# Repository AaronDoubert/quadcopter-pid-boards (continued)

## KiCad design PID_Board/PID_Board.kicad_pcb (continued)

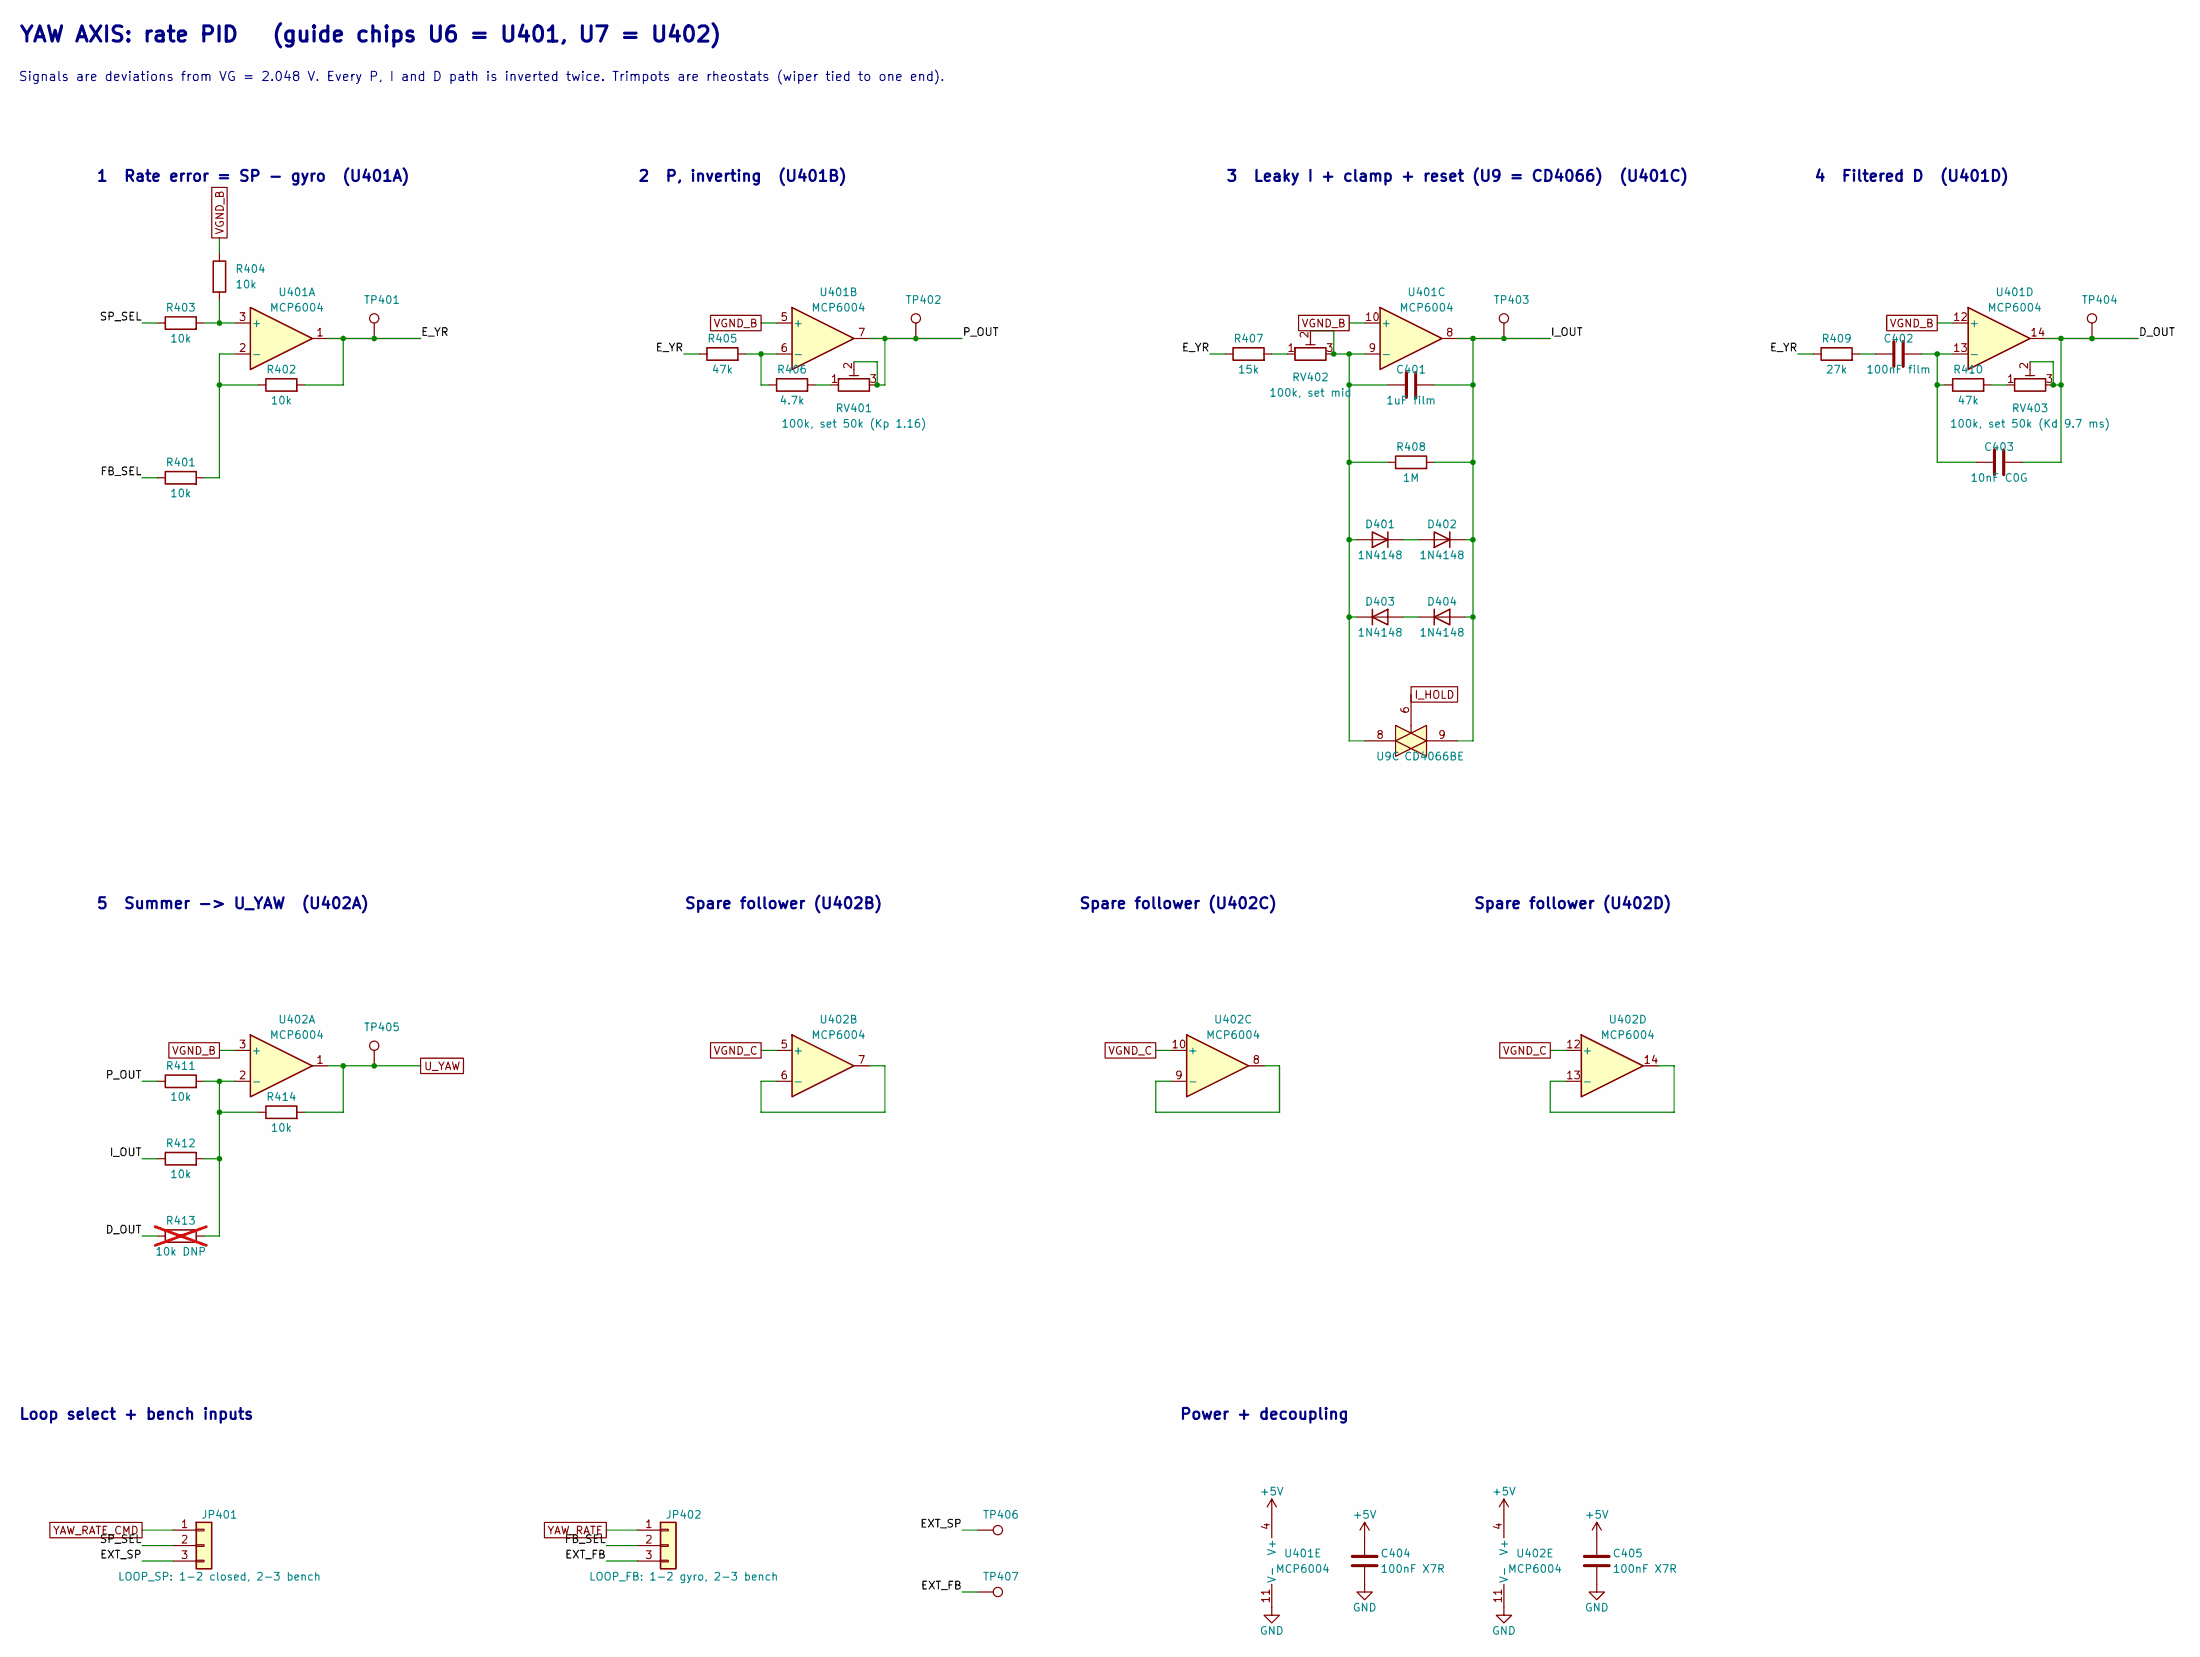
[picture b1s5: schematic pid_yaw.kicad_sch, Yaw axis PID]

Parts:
C401: 1uF film; C_Rect_L7.2mm_W5.5mm_P5.00mm_FKS2_FKP2_MKS2_MKP2
C402: 100nF film; C_Rect_L7.2mm_W2.5mm_P5.00mm_FKS2_FKP2_MKS2_MKP2
C403: 10nF C0G; C_Disc_D5.0mm_W2.5mm_P5.00mm
C404, C405: 100nF X7R; C_Disc_D5.0mm_W2.5mm_P5.00mm
D401, D402, D403, D404: 1N4148; D_DO-35_SOD27_P7.62mm_Horizontal
JP401: LOOP_SP: 1-2 closed, 2-3 bench; PinHeader_1x03_P2.54mm_Vertical
JP402: LOOP_FB: 1-2 gyro, 2-3 bench; PinHeader_1x03_P2.54mm_Vertical
R401, R402, R403, R404, R411, R412, R414: 10k; R_Axial_DIN0207_L6.3mm_D2.5mm_P7.62mm_Horizontal
R405, R410: 47k; R_Axial_DIN0207_L6.3mm_D2.5mm_P7.62mm_Horizontal
R406: 4.7k; R_Axial_DIN0207_L6.3mm_D2.5mm_P7.62mm_Horizontal
R407: 15k; R_Axial_DIN0207_L6.3mm_D2.5mm_P7.62mm_Horizontal
R408: 1M; R_Axial_DIN0207_L6.3mm_D2.5mm_P7.62mm_Horizontal
R409: 27k; R_Axial_DIN0207_L6.3mm_D2.5mm_P7.62mm_Horizontal
R413: 10k DNP; R_Axial_DIN0207_L6.3mm_D2.5mm_P7.62mm_Horizontal; not fitted
RV401: 100k, set 50k (Kp 1.16); Potentiometer_Bourns_3296W_Vertical
RV402: 100k, set mid; Potentiometer_Bourns_3296W_Vertical
RV403: 100k, set 50k (Kd 9.7 ms); Potentiometer_Bourns_3296W_Vertical
TP401: E_YR; PinHeader_1x01_P2.54mm_Vertical
TP402: P_OUT; PinHeader_1x01_P2.54mm_Vertical
TP403: I_OUT; PinHeader_1x01_P2.54mm_Vertical
TP404: D_OUT; PinHeader_1x01_P2.54mm_Vertical
TP405: U_YAW; PinHeader_1x01_P2.54mm_Vertical
TP406: EXT_SP; PinHeader_1x01_P2.54mm_Vertical
TP407: EXT_FB; PinHeader_1x01_P2.54mm_Vertical
U9: CD4066BE; DIP-14_W7.62mm
U401, U402: MCP6004; DIP-14_W7.62mm

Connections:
+5V: C404.1, C405.1, U401.4 (V+), U402.4 (V+); also elsewhere on the board
/PID_Yaw/D_OUT: C403.2, R413.1, RV403.2, RV403.3, TP404.1, U401.14
/PID_Yaw/EXT_FB: JP402.3, TP407.1
/PID_Yaw/EXT_SP: JP401.3, TP406.1
/PID_Yaw/E_YR: R402.2, R405.1, R407.1, R409.1, TP401.1, U401.1
/PID_Yaw/FB_SEL: JP402.2, R401.1
/PID_Yaw/I_OUT: C401.2, D402.1 (K), D404.2 (A), R408.2, R412.1, TP403.1, U9.9, U401.8
/PID_Yaw/P_OUT: R411.1, RV401.2, RV401.3, TP402.1, U401.7
/PID_Yaw/SP_SEL: JP401.2, R403.1
GND: C404.2, C405.2, U401.11 (V-), U402.11 (V-); also elsewhere on the board
I_HOLD: U9.6; also elsewhere on the board
unnamed: C402.1, R409.2
unnamed: C401.1, D401.2 (A), D403.1 (K), R408.1, RV402.2, RV402.3, U9.8, U401.9 (-)
unnamed: D401.1 (K), D402.2 (A)
unnamed: D403.2 (A), D404.1 (K)
unnamed: R406.2, RV401.1
unnamed: R407.2, RV402.1
unnamed: R410.2, RV403.1
unnamed: R403.2, R404.2, U401.3 (+)
unnamed: R401.2, R402.1, U401.2 (-)
unnamed: R405.2, R406.1, U401.6 (-)
unnamed: C402.2, C403.1, R410.1, U401.13 (-)
unnamed: R411.2, R412.2, R413.2, R414.1, U402.2 (-)
unnamed: U402.6 (-), U402.7
unnamed: U402.8, U402.9 (-)
unnamed: U402.13 (-), U402.14
U_YAW: R414.2, TP405.1, U402.1; also elsewhere on the board
VGND_B: R404.1, U401.5 (+), U401.10 (+), U401.12 (+), U402.3 (+); also elsewhere on the board
VGND_C: U402.5 (+), U402.10 (+), U402.12 (+); also elsewhere on the board
YAW_RATE: JP402.1; also elsewhere on the board
YAW_RATE_CMD: JP401.1; also elsewhere on the board

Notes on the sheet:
YAW AXIS: rate PID (guide chips U6 = U401, U7 = U402)
Signals are deviations from VG = 2.048 V. Every P, I and D path is inverted twice. Trimpots are rheostats (wiper tied to one end).
1 Rate error = SP - gyro (U401A)
2 P, inverting (U401B)
3 Leaky I + clamp + reset (U9 = CD4066) (U401C)
4 Filtered D (U401D)
5 Summer -> U_YAW (U402A)
Spare follower (U402B)
Spare follower (U402C)
Spare follower (U402D)
Loop select + bench inputs
Power + decoupling

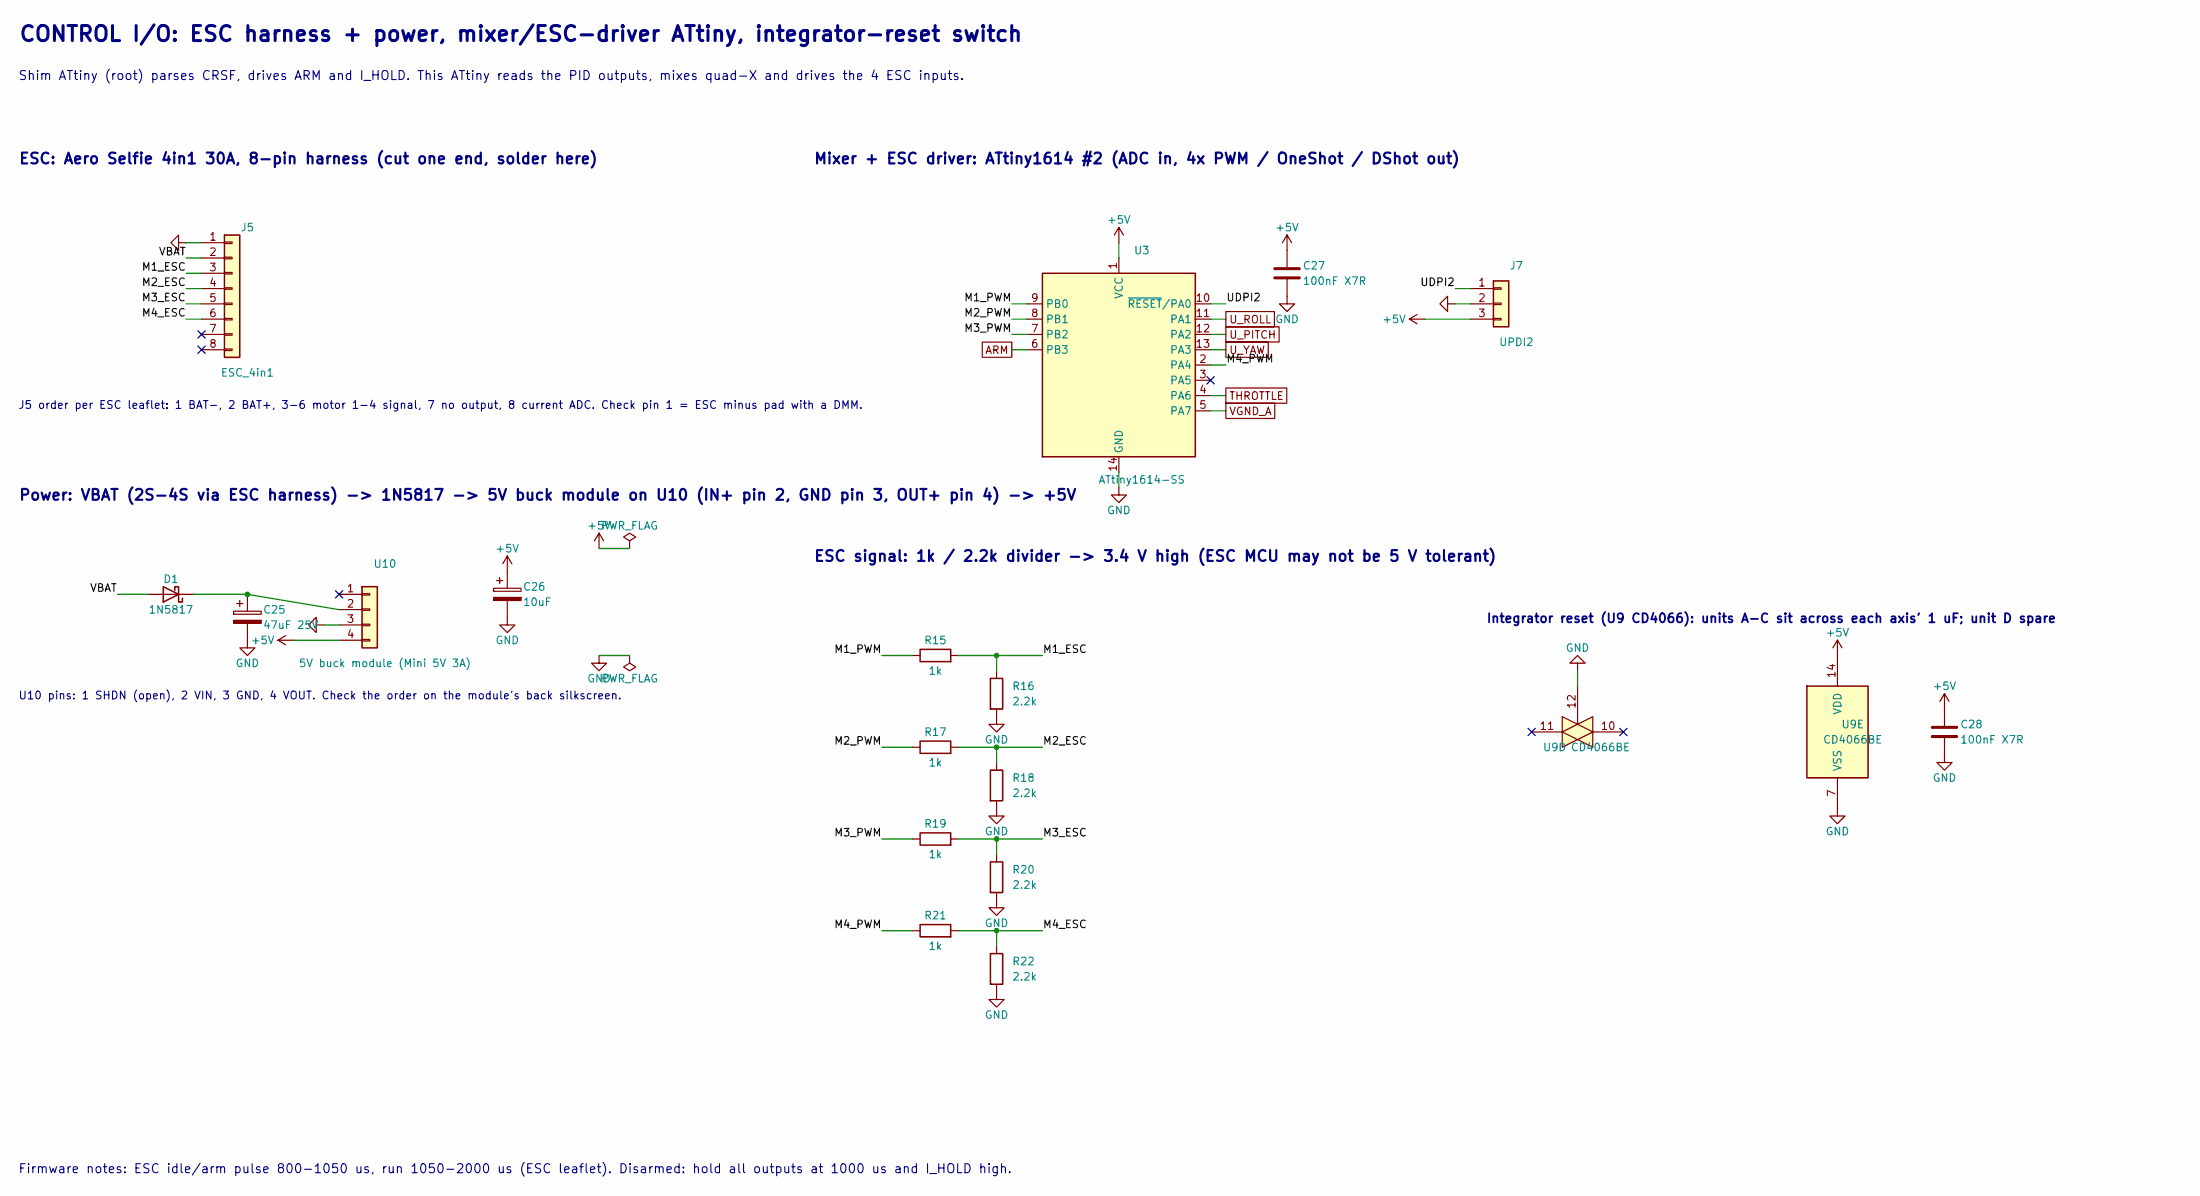
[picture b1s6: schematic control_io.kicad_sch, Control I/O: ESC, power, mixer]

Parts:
C25: 47uF 25V; CP_Radial_D5.0mm_P2.00mm
C26: 10uF; CP_Radial_D5.0mm_P2.00mm
C27, C28: 100nF X7R; C_Disc_D5.0mm_W2.5mm_P5.00mm
D1: 1N5817; D_DO-41_SOD81_P10.16mm_Horizontal
J5: ESC_4in1; PinHeader_1x08_P2.54mm_Vertical
J7: UPDI2; PinHeader_1x03_P2.54mm_Vertical
R15, R17, R19, R21: 1k; R_Axial_DIN0207_L6.3mm_D2.5mm_P7.62mm_Horizontal
R16, R18, R20, R22: 2.2k; R_Axial_DIN0207_L6.3mm_D2.5mm_P7.62mm_Horizontal
U3: ATtiny1614-SS; SOIC-14_3.9x8.7mm_P1.27mm
U9: CD4066BE; DIP-14_W7.62mm
U10: 5V buck module (Mini 5V 3A); PinHeader_1x04_P2.54mm_Vertical

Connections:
+5V: C26.1, C27.1, C28.1, J7.3, U3.1 (VCC), U9.14 (VDD), U10.4; also elsewhere on the board
/Control_IO/M1_ESC: J5.3, R15.2, R16.1
/Control_IO/M1_PWM: R15.1, U3.9 (PB0)
/Control_IO/M2_ESC: J5.4, R17.2, R18.1
/Control_IO/M2_PWM: R17.1, U3.8 (PB1)
/Control_IO/M3_ESC: J5.5, R19.2, R20.1
/Control_IO/M3_PWM: R19.1, U3.7 (PB2)
/Control_IO/M4_ESC: J5.6, R21.2, R22.1
/Control_IO/M4_PWM: R21.1, U3.2 (PA4)
/Control_IO/UDPI2: J7.1, U3.10 (~RESET/PA0)
/Control_IO/VBAT: D1.2 (A), J5.2
ARM: U3.6 (PB3); also elsewhere on the board
GND: C25.2, C26.2, C27.2, C28.2, J5.1, J7.2, R16.2, R18.2, R20.2, R22.2, U3.14 (GND), U9.7 (VSS), U9.12, U10.3; also elsewhere on the board
unnamed: C25.1, D1.1 (K), U10.2
THROTTLE: U3.4 (PA6); also elsewhere on the board
U_PITCH: U3.12 (PA2); also elsewhere on the board
U_ROLL: U3.11 (PA1); also elsewhere on the board
U_YAW: U3.13 (PA3); also elsewhere on the board
VGND_A: U3.5 (PA7); also elsewhere on the board

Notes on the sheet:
CONTROL I/O: ESC harness + power, mixer/ESC-driver ATtiny, integrator-reset switch
Shim ATtiny (root) parses CRSF, drives ARM and I_HOLD. This ATtiny reads the PID outputs, mixes quad-X and drives the 4 ESC inputs.
ESC: Aero Selfie 4in1 30A, 8-pin harness (cut one end, solder here)
J5 order per ESC leaflet: 1 BAT-, 2 BAT+, 3-6 motor 1-4 signal, 7 no output, 8 current ADC. Check pin 1 = ESC minus pad with a DMM.
Power: VBAT (2S-4S via ESC harness) -> 1N5817 -> 5V buck module on U10 (IN+ pin 2, GND pin 3, OUT+ pin 4) -> +5V
U10 pins: 1 SHDN (open), 2 VIN, 3 GND, 4 VOUT. Check the order on the module's back silkscreen.
Mixer + ESC driver: ATtiny1614 #2 (ADC in, 4x PWM / OneShot / DShot out)
ESC signal: 1k / 2.2k divider -> 3.4 V high (ESC MCU may not be 5 V tolerant)
Integrator reset (U9 CD4066): units A-C sit across each axis' 1 uF; unit D spare
Firmware notes: ESC idle/arm pulse 800-1050 us, run 1050-2000 us (ESC leaflet). Disarmed: hold all outputs at 1000 us and I_HOLD high.

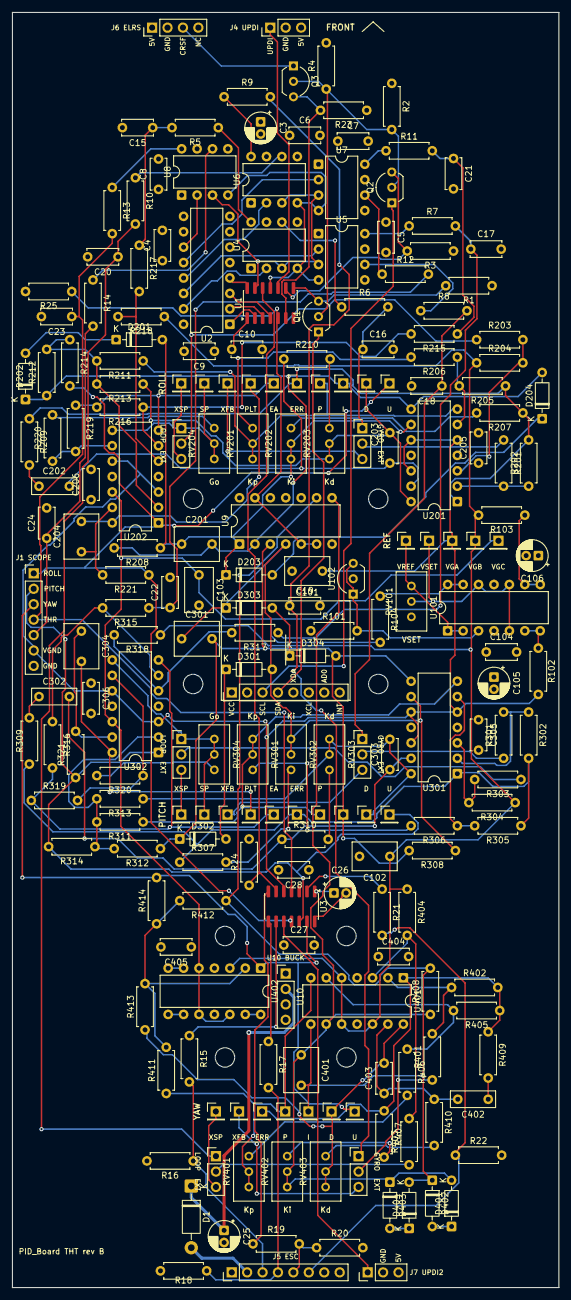
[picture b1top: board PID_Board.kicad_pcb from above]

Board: 4 copper layers, 90.0 x 210.0 mm, 228 parts (0 on the bottom side), 144 nets.

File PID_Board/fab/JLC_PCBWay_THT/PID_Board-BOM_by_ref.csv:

"Refs","Value","Footprint","Qty","DNP"
"C3-C10,C15-C28,C101-C106,C201-C206,C301-C306,C401-C405","100nF X7R,100nF film,10nF C0G,10uF,1uF,1uF film,470nF film,47uF 25V","Capacitor_THT:CP_Radial_D5.0mm_P2.00mm,Capacitor_THT:C_Disc_D5.0mm_W2.5mm_P5.00mm,Capacitor_THT:C_Rect_L7.2mm_W2.5mm_P5.00mm_FKS2_FKP2_MKS2_MKP2,Capacitor_THT:C_Rect_L7.2mm_W4.5mm_P5.00mm_FKS2_FKP2_MKS2_MKP2,Capacitor_THT:C_Rect_L7.2mm_W5.5mm_P5.00mm_FKS2_FKP2_MKS2_MKP2","45",""
"D1,D201-D204,D301-D304,D401-D404","1N4148,1N5817","Diode_THT:D_DO-35_SOD27_P7.62mm_Horizontal,Diode_THT:D_DO-41_SOD81_P10.16mm_Horizontal","13",""
"H1-H8","MountingHole","MountingHole:MountingHole_3.2mm_M3","8",""
"J1,J2,J4-J7","Axis_Mon,ELRS_RX,ESC_4in1,IMU_GY521,UPDI,UPDI2","Connector_PinHeader_2.54mm:PinHeader_1x03_P2.54mm_Vertical,Connector_PinHeader_2.54mm:PinHeader_1x04_P2.54mm_Vertical,Connector_PinHeader_2.54mm:PinHeader_1x07_P2.54mm_Vertical,Connector_PinHeader_2.54mm:PinHeader_1x08_P2.54mm_Vertical","6",""
"JP201,JP202,JP301,JP302,JP401,JP402","LOOP_FB: 1-2 gyro, 2-3 bench,LOOP_SP: 1-2 closed, 2-3 bench","Connector_PinHeader_2.54mm:PinHeader_1x03_P2.54mm_Vertical","6",""
"Q1-Q3","2N7000","Package_TO_SOT_THT:TO-92_Inline_Wide","3",""
"R1-R25,R101-R104,R201-R221,R301-R321,R401-R414","100,10k,10k DNP,15k,1M,1k,2.2k,20k,22k,27k,33k,4.7k,47k","Resistor_THT:R_Axial_DIN0207_L6.3mm_D2.5mm_P10.16mm_Horizontal","85","DNP"
"RV101,RV201-RV204,RV301-RV304,RV401-RV403","100k, set 50k (Kd 9.7 ms),100k, set 50k (Kp 1.16),100k, set 67k (Ki 10/s),100k, set mid,10k (wiper-GND 8.1k),50k, set 25k (Go 1.75)","Potentiometer_THT:Potentiometer_Bourns_3296W_Vertical","12",""
"TP101-TP105,TP201-TP210,TP301-TP310,TP401-TP407","D_OUT,EXT_FB,EXT_SP,E_A,E_PR,E_RR,E_YR,I_OUT,PITCH_RATE_SP,PLANT_OUT,P_OUT,ROLL_RATE_SP,U_PITCH,U_ROLL,U_YAW,VGND_A,VGND_B,VGND_C,VREF_BUF,VSET","Connector_PinHeader_2.54mm:PinHeader_1x01_P2.54mm_Vertical","32",""
"U1-U10,U101,U102,U201,U202,U301,U302,U401,U402","74HC138,ATtiny1614-SS,CD4066BE,MCP4822,MCP6004,Pololu D24V5F5,TL431ACLPG","Connector_PinHeader_2.54mm:PinHeader_1x04_P2.54mm_Vertical,Package_DIP:DIP-14_W7.62mm,Package_DIP:DIP-16_W7.62mm,Package_DIP:DIP-8_W7.62mm,Package_SO:SOIC-14_3.9x8.7mm_P1.27mm,Package_TO_SOT_THT:TO-92_Inline_Wide","18",""

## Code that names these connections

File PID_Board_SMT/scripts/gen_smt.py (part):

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                 ref_xy=(x + 11.43, y - 11.43), val_xy=(x + 11.43, y + 11.43), just="left")
    sh.pwr("+5V", *t["17"][:2]); sh.pwr("GND", *t["7"][:2])
    sh.expect("+5V", f"{ref}.17"); sh.expect("GND", f"{ref}.7")
    sh.pin_net(t, ref, "5", "SCL_5V")
    sh.pin_net(t, ref, "6", "SDA_5V")
    sh.pin_net(t, ref, "15", "+5V", stub=5.08)
    sh.pin_net(t, ref, "4", a0, stub=5.08)
    sh.pin_net(t, ref, "16", a1, stub=10.16)
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    sh.wire((xR, O[1]), (tpx, O[1]), (X + 22.86, O[1]))
    sh.junc(tpx, O[1])
    sh.place("Connector", "TestPoint", "TP101", "VREF_BUF", FP["TP"], tpx, O[1], 0, ref_xy=(tpx + 1.27, O[1] - 6.35), hide_val=True)
    sh.label("VREF_BUF", X + 22.86, O[1], 0)
    sh.expect("VREF_BUF", "U101.1", "U101.2", "TP101.1")
    # VSET divider: VREF_BUF - 47.5k - VSET - (U103 ch3 rheostat + 165k) - GND.
    # Code 128 (power-on) ~ 2.044 V; range 1.94..2.12 V; 0.67 mV per step.
    py = 71.12
    sh.text("VSET divider (digital trim)", 121.92, 45.72, 1.8)
    sh.wire((124.46, py), (127.0, py))
    sh.label("VREF_BUF", 124.46, py, 180)
    sh.chain([("R", "R105", "47.5k", FP["R"])], 127.0, 139.7, py, "VREF_BUF", "VSET")
    sh.wire((139.7, py), (139.7, py - 5.08))
    sh.label("VSET", 139.7, py - 5.08, 90)
    sh.chain([("DPOT", "U103", 4, "VSET trim: ch3, code 128 = 2.044 V"), ("R", "R106", "165k", FP["R"])],
             139.7, 175.26, py, "VSET", "GND")
    sh.junc(139.7, py)
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    testpoint(sh, "TP102", "VSET", 160.02, 55.88)
    t = sh.place("Device", "C", "C107", "100nF X7R", FP["C0603"], 167.64, 91.44, 0,
                 ref_xy=(170.18, 90.17), val_xy=(170.18, 92.71), just="left")
    sh.pin_net(t, "C107", "1", "VSET")
    sh.pin_net(t, "C107", "2", "GND", stub=0)
    # U103 control unit (I2C 0x2E); its channels 0-2 sit on the yaw sheet
    sh.text("U103 MCP4451: I2C 0x2E (A1=1, A0=0). ch0-2 = yaw P/I/D, ch3 = VSET", 121.92, 101.6, 1.5)
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        P, M, O = t[pp][:2], t[pm][:2], t[po][:2]
        xL, xR = X - 10.16, X + 10.16
        sh.wire(P, (xL, P[1]))
        sh.label("VSET", xL, P[1], 180)
        sh.wire(M, (xL, M[1]), (xL, M[1] + 5.08), (xR, M[1] + 5.08), (xR, O[1]))
        sh.wire(O, (xR, O[1]))
        rref, cref, tpref = f"R1{2 + i:02d}", f"C1{1 + i:02d}", f"TP1{3 + i:02d}"
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                         ref_xy=(X + 2.54, r2 - 7.62), val_xy=(X + 2.54, r2 - 5.08))
            P, M, O = t[pp][:2], t[pm][:2], t[po][:2]
            xL, xR = X - 10.16, X + 10.16
            sh.wire(P, (xL, P[1])); sh.label("VGND_C", xL, P[1], 180)
            sh.wire(M, (xL, M[1]), (xL, M[1] + 5.08), (xR, M[1] + 5.08), (xR, O[1]), O)
            sh.expect("VGND_C", f"{ub}.{pp}")
            sh.expect(f"~{ub}.{po}", f"{ub}.{po}", f"{ub}.{pm}")
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    sh.text("UPDI (Adafruit UPDI Friend)", 22.86, 40.64, 1.8)
    t = sh.place("Connector_Generic", "Conn_01x03", "J4", "UPDI", FP["H3"], 50.8, 55.88, 0,
                 ref_xy=(53.34, 49.53), val_xy=(53.34, 62.23))
    sh.pin_net(t, "J4", "1", "UDPI")
    sh.pin_net(t, "J4", "2", "GND", stub=2.54)
    sh.pin_net(t, "J4", "3", "+5V", stub=7.62)
    decouple(sh, 71.12, 55.88, "C3", "10uF 25V", FP["C0805"])
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                 ref_xy=(48.26, 92.71), val_xy=(48.26, 107.95))
    sh.pin_net(t, "J6", "1", "+5V", stub=7.62)
    sh.pin_net(t, "J6", "2", "GND", stub=2.54)
    sh.pin_net(t, "J6", "3", "CRSF_3V3")
    sh.pin_net(t, "J6", "4", None, stub=0)
    sh.text("J6: 1 5V, 2 GND, 3 receiver TX, 4 receiver RX (unused)", 22.86, 113.03, 1.3, False)
    qx, qy = 66.04, 88.9
    t = sh.place("Transistor_FET", "Q_NMOS_GSD", "Q3", "BSS138", FP["SOT23"], qx, qy, 270,
                 ref_xy=(qx + 3.81, qy + 6.35), val_xy=(qx + 3.81, qy + 8.89))
    G, S, Dn = t["1"][:2], t["2"][:2], t["3"][:2]   # SOT-23: 1 G, 2 S, 3 D
    sh.wire(S, (S[0] - 5.08, S[1])); sh.label("CRSF_3V3", S[0] - 5.08, S[1], 180)
    sh.wire(G, (G[0], G[1] - 2.54)); sh.label("GATE_BIAS", G[0], G[1] - 2.54, 90)
    node = (Dn[0] + 7.62, Dn[1])
    sh.wire(Dn, node, (node[0] + 5.08, node[1])); sh.junc(*node)
    sh.label("CRSF_5V", node[0] + 5.08, node[1], 0)
    top, bot, _ = sh.two("R", "R23", "2.2k", FP["R"], node[0], node[1] - 7.62, horizontal=False)
    sh.wire(bot, node); sh.pwr("+5V", *top)
    sh.expect("CRSF_3V3", "Q3.2"); sh.expect("GATE_BIAS", "Q3.1"); sh.expect("CRSF_5V", "Q3.3", "R23.2")
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                 ref_xy=(302.26, 55.88), val_xy=(302.26, 80.01))
    sh.pin_net(t, "J2", "1", "+5V", stub=7.62)
    sh.pin_net(t, "J2", "2", "GND", stub=2.54)
    sh.pin_net(t, "J2", "3", "SCL_3V3")
    sh.pin_net(t, "J2", "4", "SDA_3V3")
    for num in ("5", "6", "7", "8"):
        sh.pin_net(t, "J2", num, None, stub=0)
    sh.text("J2 = GY-521 header: 1 VCC, 2 GND, 3 SCL, 4 SDA; 5-8 (XDA XCL AD0 INT) mechanical only", 279.4, 86.36, 1.3, False)
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    sh.wire(bot, mid, top2)
    sh.pwr("GND", *bot2); sh.expect("GND", "R4.2")
    sh.wire(mid, (gx + 5.08, mid[1])); sh.junc(*mid)
    sh.label("GATE_BIAS", gx + 5.08, mid[1], 0)
    sh.expect("GATE_BIAS", "R2.2", "R4.1")
    for i, (q, pu, low, high) in enumerate([("Q1", "R1", "SDA_3V3", "SDA_5V"), ("Q2", "R3", "SCL_3V3", "SCL_5V")]):
        qx, qy = 365.76, 63.5 + 30.48 * i
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                     ref_xy=(qx + 3.81, qy + 6.35), val_xy=(qx + 3.81, qy + 8.89))
        G, S, Dn = t["1"][:2], t["2"][:2], t["3"][:2]   # SOT-23: 1 G, 2 S, 3 D
        sh.wire(S, (S[0] - 5.08, S[1])); sh.label(low, S[0] - 5.08, S[1], 180)
        sh.wire(G, (G[0], G[1] - 2.54)); sh.label("GATE_BIAS", G[0], G[1] - 2.54, 90)
        node = (Dn[0] + 7.62, Dn[1])
        sh.wire(Dn, node, (node[0] + 7.62, node[1])); sh.junc(*node)
        sh.label(high, node[0] + 7.62, node[1], 0)
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    decouple(sh, X + 27.94, Y - 15.24, "C27", "100nF X7R")
    t = sh.place("Connector_Generic", "Conn_01x03", "J7", "UPDI2", FP["H3"], 266.7, 66.04, 0,
                 ref_xy=(269.24, 59.69), val_xy=(269.24, 72.39))
    sh.pin_net(t, "J7", "1", "UDPI2")
    sh.pin_net(t, "J7", "2", "GND", stub=2.54)
    sh.pin_net(t, "J7", "3", "+5V", stub=7.62)

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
